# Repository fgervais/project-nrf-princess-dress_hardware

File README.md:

# Princess Dress

## Motherboard

## Firmware

https://github.com/fgervais/project-nrf-princess-dress

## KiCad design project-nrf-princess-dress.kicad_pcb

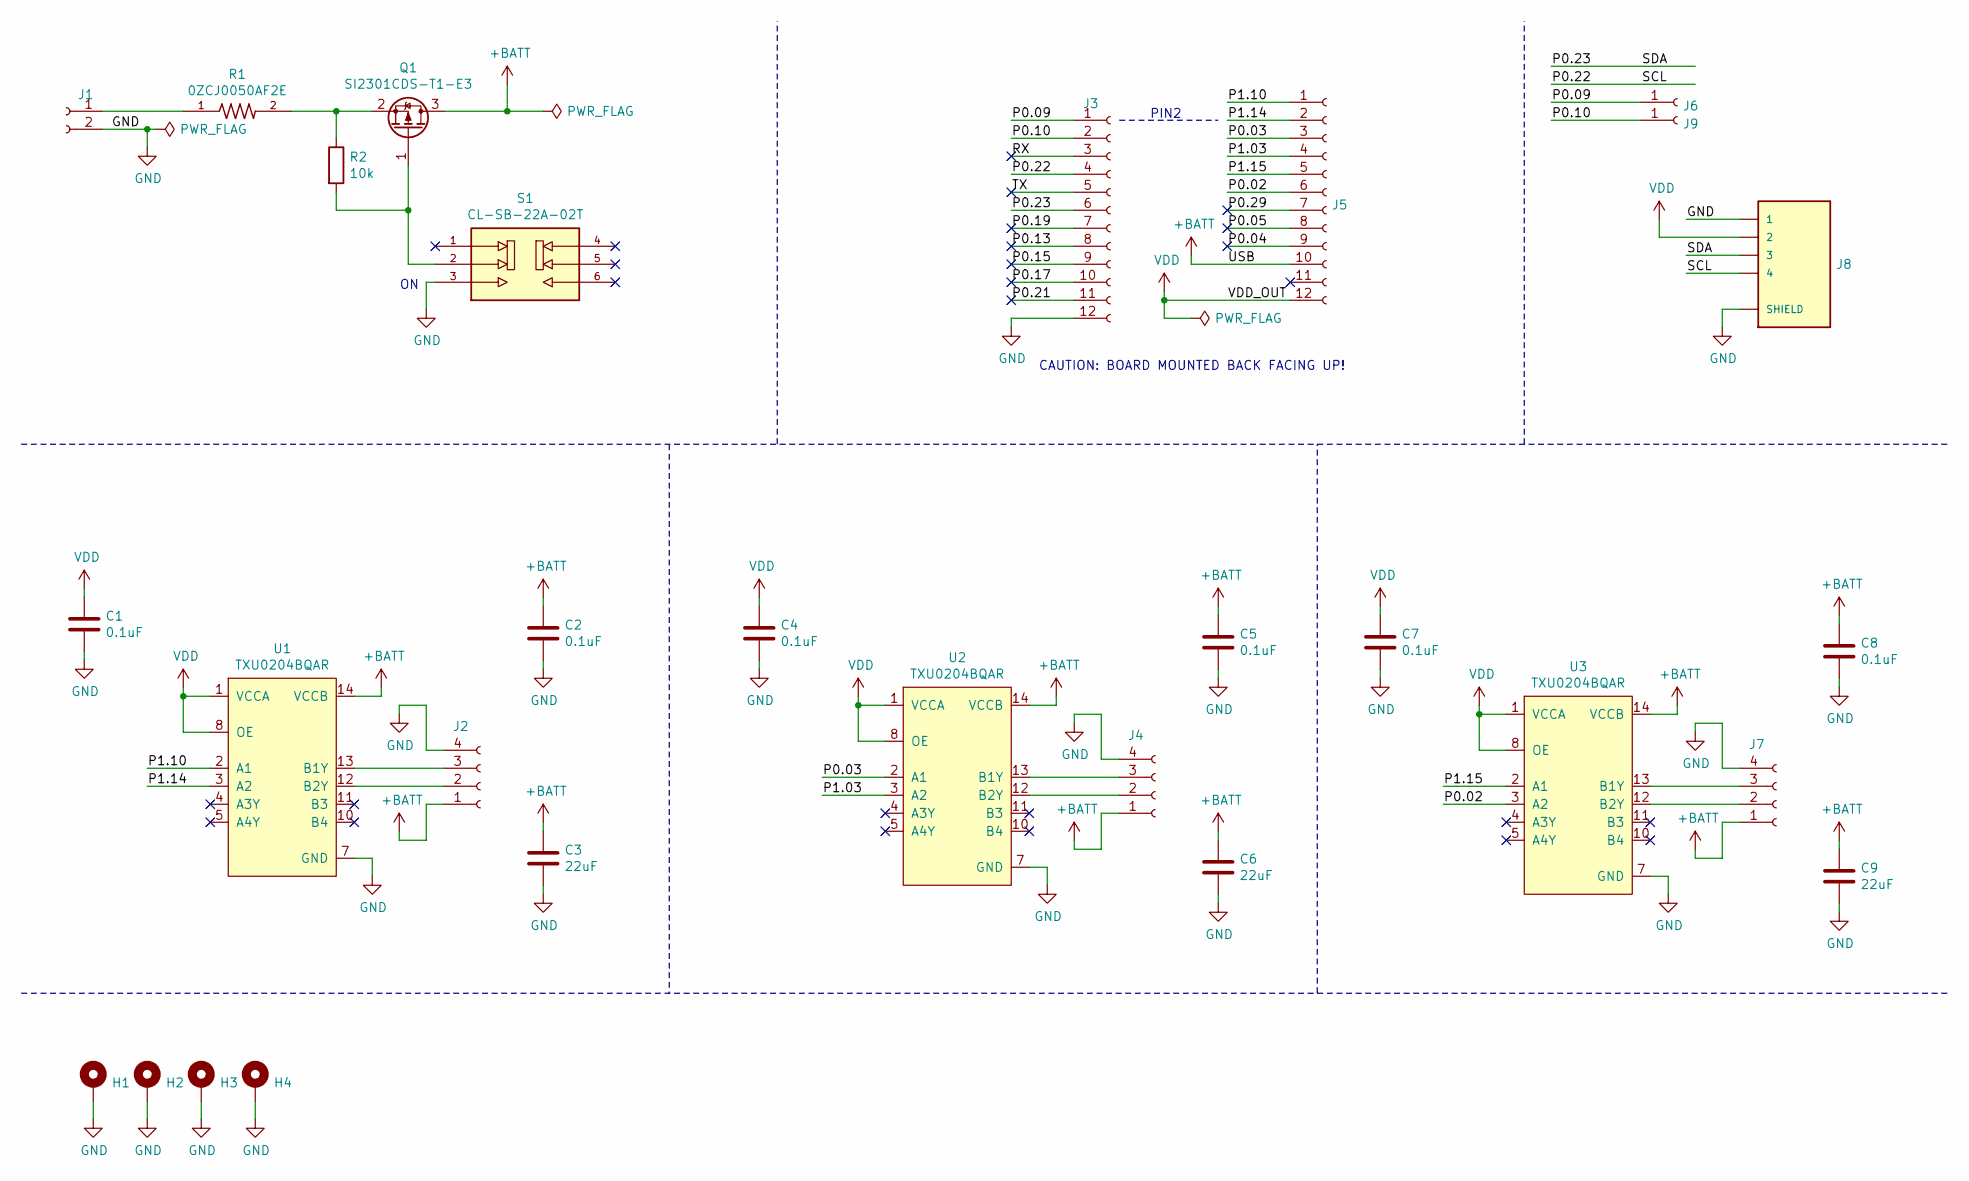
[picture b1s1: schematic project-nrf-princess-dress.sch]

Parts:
C1, C2, C4, C5, C7, C8: 0.1uF; C_0603_1608Metric
C3, C6, C9: 22uF; C_1210_3225Metric
H1, H2, H3, H4: MountingHole_Pad; MountingHole_2.7mm_M2.5_ISO7380_Pad
J1: Conn_01x02_Female; TZ022101B000G
J2, J4, J7: Conn_01x04_Female; TZ042101B000G
J3, J5: Conn_01x12_Female; PinSocket_1x12_P2.54mm_Vertical_SMD_Pin1Right
J6, J9: Conn_01x01_Female; SolderWirePad_1x01_SMD_5x10mm
J8: SM04B-SRSS-TB(LF)(SN); JST_SM04B-SRSS-TB(LF)(SN)
Q1: SI2301CDS-T1-E3; SOT-23
R1: 0ZCJ0050AF2E; RESC3216X125N
R2: 10k; R_0603_1608Metric
S1: CL-SB-22A-02T; SW_CL-SB-22A-02T; PARTREV N/A
U1, U2, U3: TXU0204BQAR

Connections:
+BATT: C2.1, C3.1, C5.1, C6.1, C8.1, C9.1, J2.1, J4.1, J5.10, J7.1, Q1.3 (D), U1.14 (VCCB), U2.14 (VCCB), U3.14 (VCCB)
/P0.02: J5.6, U3.3 (A2)
/P0.03: J5.3, U2.2 (A1)
/P0.04: J5.9
/P0.05: J5.8
/P0.09: J3.1, J6.1
/P0.10: J3.2, J9.1
/P0.13: J3.8
/P0.15: J3.9
/P0.17: J3.10
/P0.19: J3.7
/P0.21: J3.11
/P0.22: J3.4, J8.4
/P0.23: J3.6, J8.3
/P0.29: J5.7
/P1.03: J5.4, U2.3 (A2)
/P1.10: J5.1, U1.2 (A1)
/P1.14: J5.2, U1.3 (A2)
/P1.15: J5.5, U3.2 (A1)
/RX: J3.3
/TX: J3.5
GND: C1.2, C2.2, C3.2, C4.2, C5.2, C6.2, C7.2, C8.2, C9.2, H1.1, H2.1, H3.1, H4.1, J1.2, J2.4, J3.12, J4.4, J7.4, J8.1, J8.S1 (SHIELD), J8.S2 (SHIELD), S1.3, U1.7 (GND), U2.7 (GND), U3.7 (GND)
unnamed: J1.1, R1.1
unnamed: J2.2, U1.12 (B2Y)
unnamed: J2.3, U1.13 (B1Y)
unnamed: J4.2, U2.12 (B2Y)
unnamed: J4.3, U2.13 (B1Y)
unnamed: J7.2, U3.12 (B2Y)
unnamed: J7.3, U3.13 (B1Y)
unnamed: Q1.1 (G), R2.2, S1.2
unnamed: Q1.2 (S), R1.2, R2.1
VDD: C1.1, C4.1, C7.1, J5.12, J8.2, U1.1 (VCCA), U1.8 (OE), U2.1 (VCCA), U2.8 (OE), U3.1 (VCCA), U3.8 (OE)

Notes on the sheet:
PIN2
CAUTION: BOARD MOUNTED BACK FACING UP!

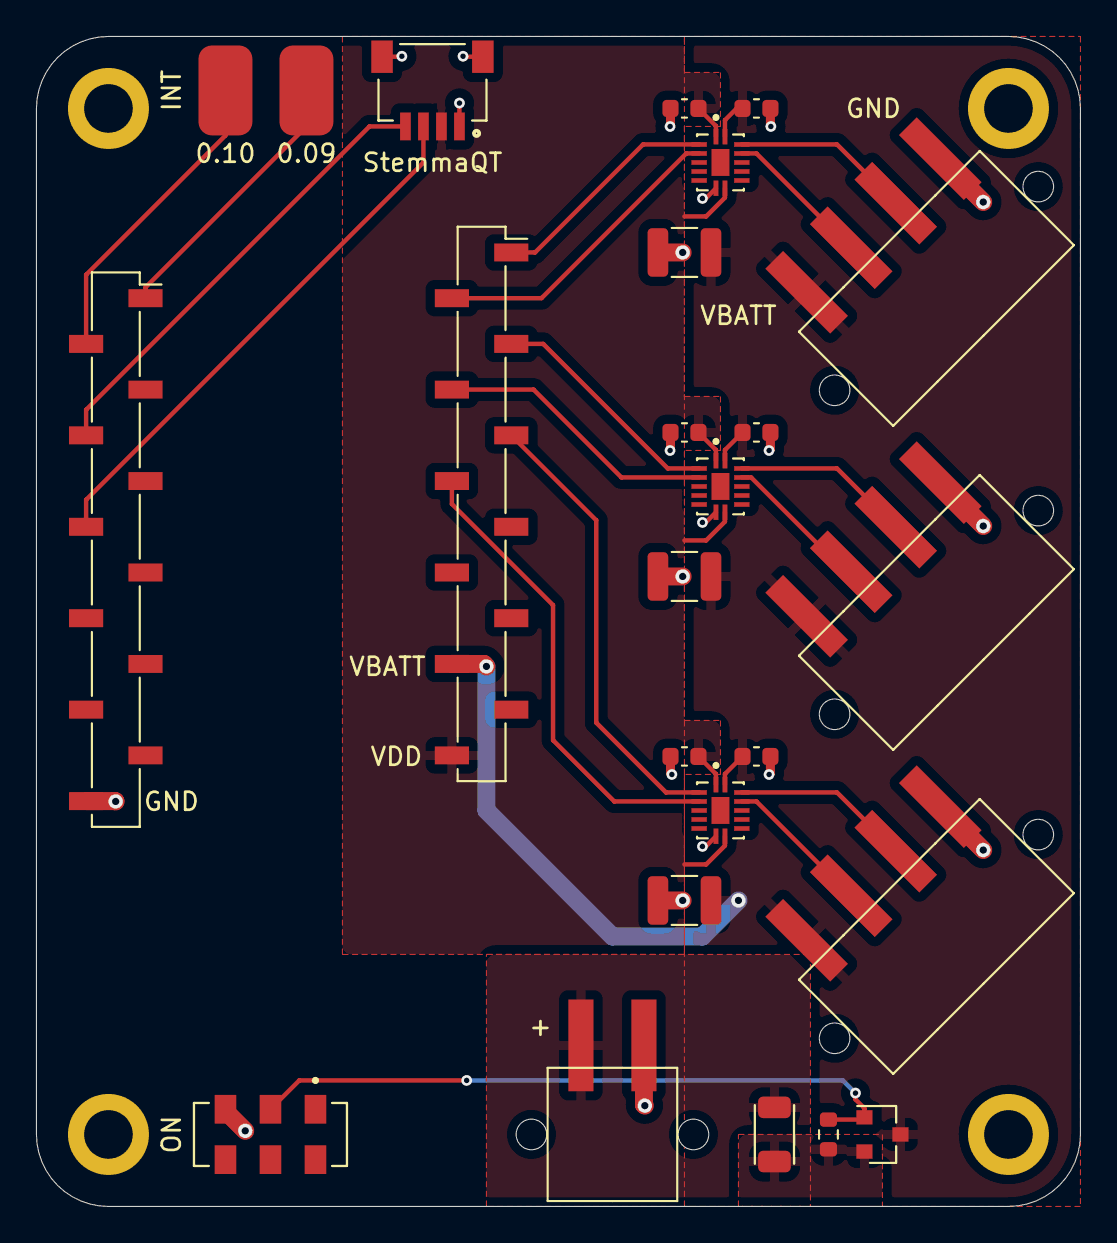
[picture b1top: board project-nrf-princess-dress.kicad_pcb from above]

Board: 2 copper layers, 58.0 x 65.0 mm, 29 parts (0 on the bottom side), 22 nets.

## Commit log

2022-11-02 Empty kicad project
2022-11-03 Update libs
2022-11-03 Add a piece to the sch
2022-11-04 First schematic draft
2022-11-04 Add mounting holes
2022-11-06 First placement
2022-11-06 Move the voltage translator blocks up
2022-11-06 Change i2c pins order
2022-12-05 Routing
2022-12-05 Add power input planes
2022-12-06 Routing done
2022-12-06 Add silk
2022-12-13 Add a pad for the ism330dhcx int2
2022-12-13 Change the PMOS value
2023-01-01 Save PCB in kicad 6
2023-01-01 Add v1.0.0 tag to silkscreen
2023-01-01 Add gerbers
2023-01-01 Ignore backups
2023-02-05 Add assembly file
2023-03-04 Add motherboard view
2023-03-04 Add firmware link
